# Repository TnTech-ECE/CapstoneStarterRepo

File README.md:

# Drone Tracking System
## Executive Summary

Drones have grown exceedingly popular in recent years due to both their novelty and capabilities. Unfortunately, not all drone users prioritize the safety and privacy of others while flying their drones, so to combat a rise in unsafe drone activities, the Federal Aviation Administration (FAA) created a regulation in 2023 requiring drones to emit a remote identification signal. Utilizing this regulation, this team is designing a drone tracking device that will notify the Tennessee Technological University (TTU) Police if an unauthorized drone enters the contiguous campus.

## Capabilities

The Drone tracker system is capable of storing RID information into a database. The database can send the required RID data to the camera where the camera uses it to point at a target. The camera then takes a picture and sends the image back to the database. The website will display the RID data from the database as well as a map of the target locations.

## Project Demonstration & Images
Project Demonstration Video

https://github.com/user-attachments/assets/e732b90d-667f-4436-8810-12add2868be1

https://github.com/user-attachments/assets/4852f584-2c88-4b63-8bfe-9ffbe9ff3a57

https://github.com/user-attachments/assets/bf1db036-6065-4abe-843b-16f495730f5c

#### Other video links:
[Camera Software System minimal functional prototype](https://www.youtube.com/shorts/UNsuytf4N7U)

[Website system](https://www.youtube.com/watch?v=dnVWmRdjKF0)

## About Us

### Team

From left to right:

[JieJun Stowell](https://www.linkedin.com/in/jiejun-s-4b34a8132/) is an computer engineering major student at Tennessee Technological University. He is intrestested in embedded system design development.

[Abe Perkins](https://www.linkedin.com/in/abraham-perkins-7436a6204/) is a student at Tennessee Technological University with major in computer engineering and a minor in math. His interests include hardware security, computer architecture, and machine learning. 

[Austin Williams](https://www.linkedin.com/in/austingwilliams/) is an electrical engineering major with a concentration in Power Systems. He is interested in power transmission and operations.

[Aaron Stewart](https://www.linkedin.com/in/aaronjs124) is an electrical engineering major with a concentration in Control Systems. He is interested in industrial production systems, mechatronics, and additive manufacturing methods.

[Sterling Sloan](https://www.linkedin.com/in/sterling-sloan-a848642a0/) is an electrical engineering major at Tennessee Technological University. He has interests in signal processing and optoelectronics.

[Meredith Nye](https://www.linkedin.com/in/meredith-nye-89455a1b5) is an electrical engineering major, mechatronics concentration and student-athlete at Tennessee Technological University with minors in math and biology. She is interested in prosthetics design, biomechanical engineering, and robotics.

### Faculty Supervisor

Dr. Jeffrey Austen is the faculty supervisor and stakeholder for the drone tracker project. He is a professor with the Electrical and Computer Engineering Department at Tennessee Technological University with specializations in signal processing and communication systems.

### Stakeholders

Dr. Jeffrey Austen

Tennessee Technological University Police

### Recognitions

We would like to recognize and thank Dr.Jeffrey Austen for his guidance and support as well as the [Spring 2024 Base Modular Robot Team](https://github.com/TnTech-ECE/Spring2024-Base-Modular-Robot) for their repository organization inspiration.

## Repo Organization

### [Reports](/Reports)
  - [Project Proposal](https://github.com/mrnye42/S24_Team1_DroneTracker/blob/main/Reports/Project%20Proposal%20Revisions.pdf) :the initial document for the project where the problem is defined and the goals for the project.
  - [Conceptual Design and Planning](https://github.com/mrnye42/S24_Team1_DroneTracker/blob/main/Reports/Conceptual%20Design%20and%20Planning%20Final.pdf) :gives a more detailed solution to the problem as well as subsystem breakdowns and a projected timeline and budget.
  - [Final Presentation](https://github.com/mrnye42/S24_Team1_DroneTracker/blob/main/Reports/Drone%20Tracker%20IAB%20Presentation%20Final.pdf) :a pdf version of the PowerPoint presentation given to the Advisory Board that showcases the entire project and contains video links to project demonstrations. 
  - [Poster](https://github.com/mrnye42/S24_Team1_DroneTracker/blob/main/Reports/Poster.pdf) :showcases the entire project. Was displayed at the senior design expo and will be framed in Brown Hall.
  - [Lessons Learned Presentations](/Reports/Lessons-Learned-Presentations) :folder contains a few of the team's individual lessons learned PowerPoint presentations and contain things that went wrong and advice for future students.

### [Documentation](/Documentation)
All documentation for the project is included in the above folder. Documentation includes all schematics, images, models, BOM, and designs used in the project.

The [Meeting Minutes](/Documentation/Meeting-Minutes) folder contains the dated minutes from weekly meetings and allows a quick view into the progress of the team.

[Signoffs](/Documentation/Signoffs) are used to finalize designs for each subsystem. This includes schematics, design decisions, BOM, and analysis.

The [Experimentation](/Documentation/Experimentation/) folder contains individual markdown files detailing experiments done by the team in order to prove the adherence to different system constraints.

The [Minimal Functionality Prototype document](https://github.com/mrnye42/S24_Team1_DroneTracker/blob/main/Documentation/Minimal%20Functionality%20Prototype%20Signoffs.pdf) contains the proposed minimal functionality requirements for the protype as well as Dr.Austen's feedback on them.

The [Final BOM](https://github.com/mrnye42/S24_Team1_DroneTracker/blob/main/Documentation/Final%20BOM.pdf) pdf contains all the ordered parts for the project.

The [Project Photos](/Documentation/Project-Photos) folder contains any photos (not technical images) from the project. Includes addtional pictures of the team.

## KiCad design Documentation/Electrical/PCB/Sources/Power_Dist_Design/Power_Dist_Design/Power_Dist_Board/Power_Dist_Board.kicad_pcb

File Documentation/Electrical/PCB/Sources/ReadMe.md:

- This contains the gerber files in order to purchase the input and error subsystem PCBs.
- ## Relevant design notes
- The polarity shown on the PCB design for the electrolytic capacitors is in a few cases backwards, therefore it is advised to read the traces and consult the schematic before any polarized 
  capacitors are soldered on the PCB.
- The I/O and supply ports were not placed on the PCB with ports therefore in order to connect the PCB to other elements it is recommended to consult the schematic and solder wires in the 
  appropriate places.

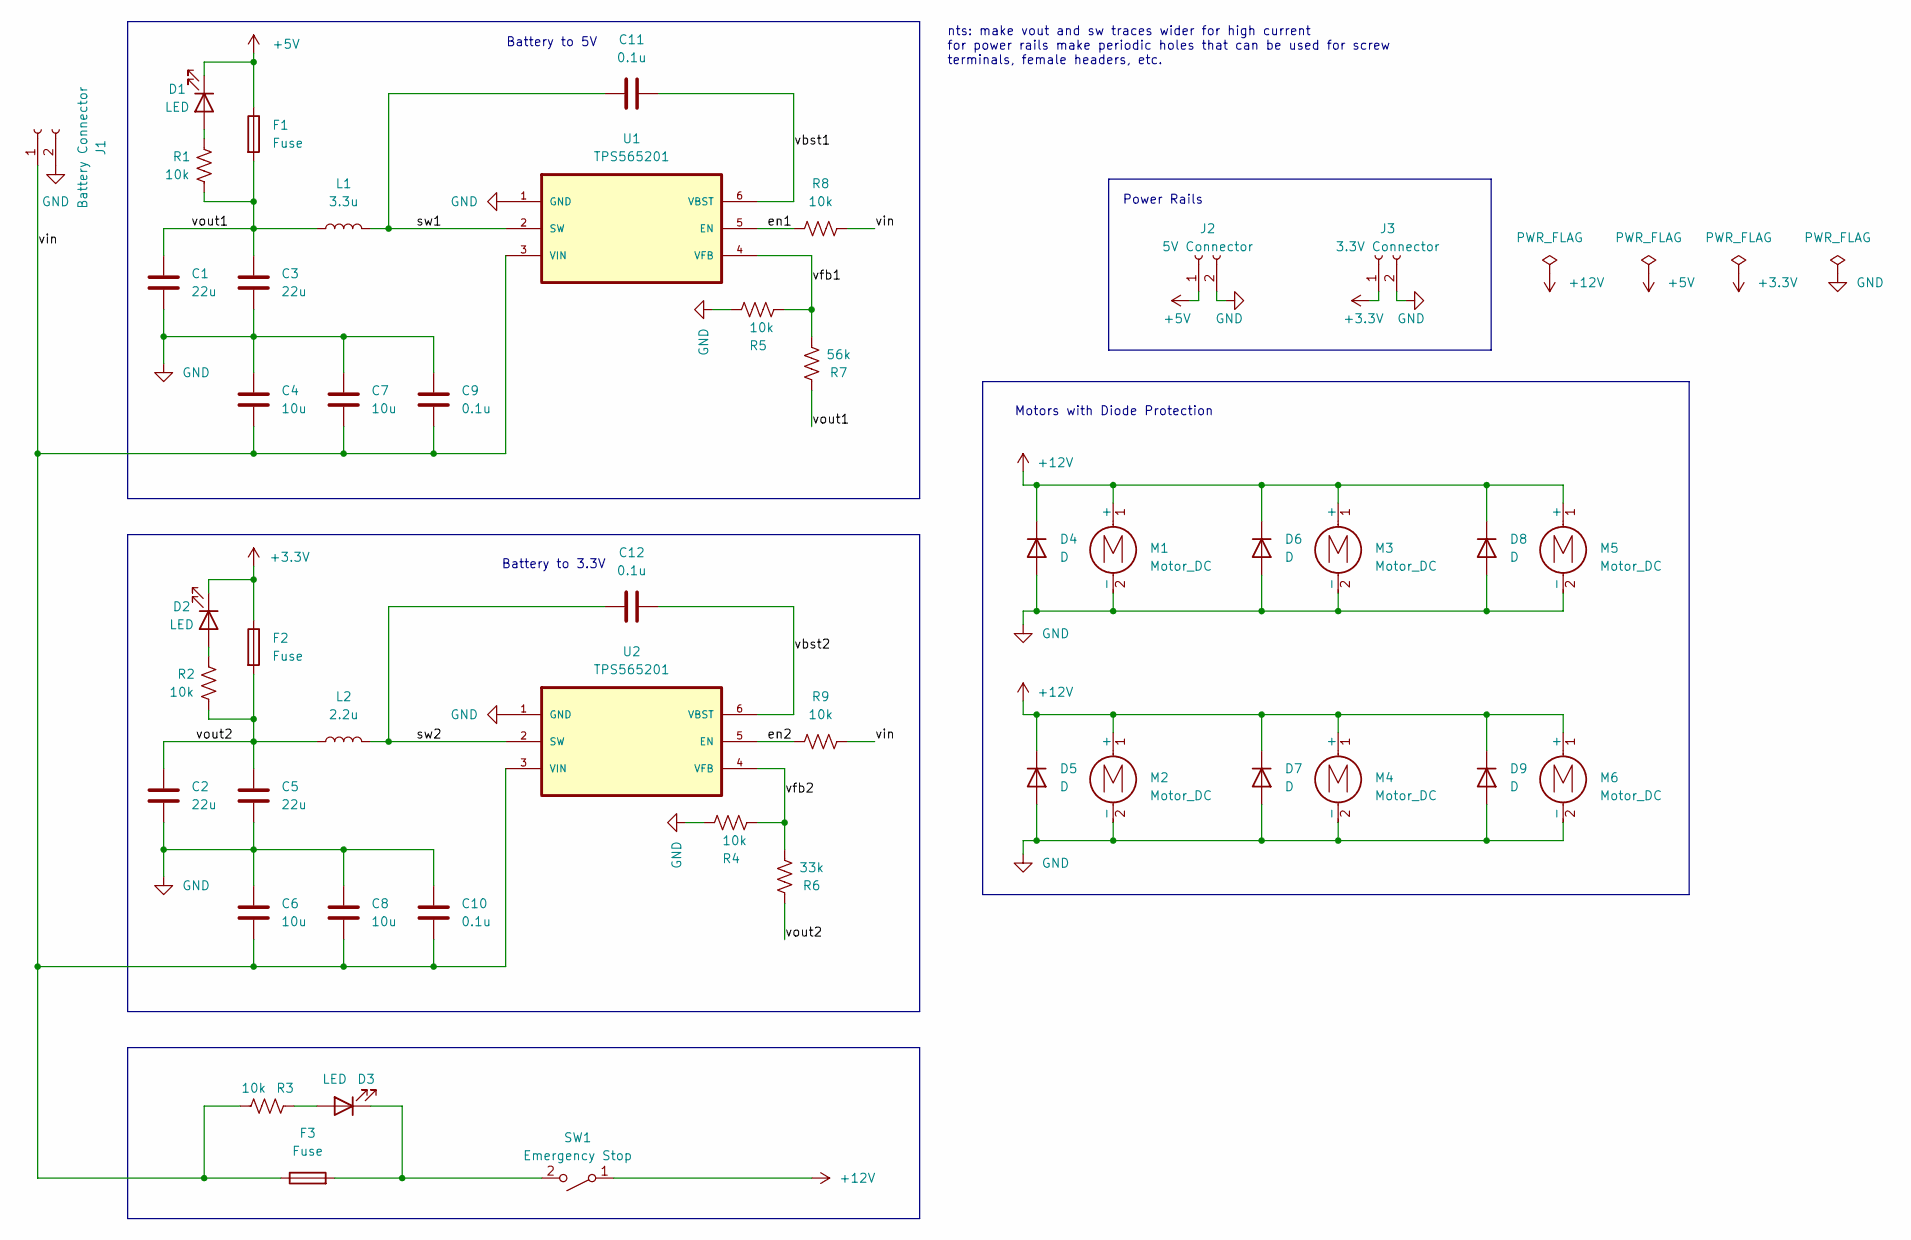
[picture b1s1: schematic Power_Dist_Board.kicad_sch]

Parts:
C1, C2, C3, C5: 22u; C_1206_3216Metric_Pad1.33x1.80mm_HandSolder
C4, C6, C7, C8: 10u; C_1206_3216Metric_Pad1.33x1.80mm_HandSolder
C9, C10, C11, C12: 0.1u; C_1206_3216Metric_Pad1.33x1.80mm_HandSolder
D1, D2, D3: LED; LED_1206_3216Metric_Pad1.42x1.75mm_HandSolder
D4, D5, D6, D7, D8, D9: D; DIO_RB051MM_ROM-M
F1, F2, F3: Fuse; Fuse_1206_3216Metric_Pad1.42x1.75mm_HandSolder
J1: Battery Connector; Molex_Screw_Term_0397730002
J2: 5V Connector; PhoenixContact_MSTBVA_2,5_2-G-5,08_1x02_P5.08mm_Vertical
J3: 3.3V Connector; PhoenixContact_MSTBVA_2,5_2-G-5,08_1x02_P5.08mm_Vertical
L1: 3.3u; R_1206_3216Metric_Pad1.30x1.75mm_HandSolder
L2: 2.2u; R_1206_3216Metric_Pad1.30x1.75mm_HandSolder
M1, M2, M3, M4, M5, M6: Motor_DC; Molex_Screw_Term_0397730002
R1, R2, R3, R4, R5, R8, R9: 10k; R_1206_3216Metric_Pad1.30x1.75mm_HandSolder
R6: 33k; R_1206_3216Metric_Pad1.30x1.75mm_HandSolder
R7: 56k; R_1206_3216Metric_Pad1.30x1.75mm_HandSolder
SW1: Emergency Stop; Molex_Screw_Term_0397730002
U1, U2: TPS565201

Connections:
+3.3V: D2.1 (K), F2.1, J3.1
+5V: D1.1 (K), F1.1, J2.1
+12V: D4.1 (K), D5.1 (K), D6.1 (K), D7.1 (K), D8.1 (K), D9.1 (K), M1.1 (+), M2.1 (+), M3.1 (+), M4.1 (+), M5.1 (+), M6.1 (+), SW1.1 (A)
/en1: R8.1, U1.5 (EN)
/en2: R9.1, U2.5 (EN)
/sw1: C11.1, L1.2, U1.2 (SW)
/sw2: C12.1, L2.2, U2.2 (SW)
/vbst1: C11.2, U1.6 (VBST)
/vbst2: C12.2, U2.6 (VBST)
/vfb1: R5.2, R7.1, U1.4 (VFB)
/vfb2: R4.2, R6.1, U2.4 (VFB)
/vin: C4.2, C6.2, C7.2, C8.2, C9.2, C10.2, F3.1, J1.1, R3.1, R8.2, R9.2, U1.3 (VIN), U2.3 (VIN)
/vout1: C1.1, C3.1, F1.2, L1.1, R1.1, R7.2
/vout2: C2.1, C5.1, F2.2, L2.1, R2.1, R6.2
GND: C1.2, C2.2, C3.2, C4.1, C5.2, C6.1, C7.1, C8.1, C9.1, C10.1, D4.2 (A), D5.2 (A), D6.2 (A), D7.2 (A), D8.2 (A), D9.2 (A), J1.2, J2.2, J3.2, M1.2 (-), M2.2 (-), M3.2 (-), M4.2 (-), M5.2 (-), M6.2 (-), R4.1, R5.1, U1.1 (GND), U2.1 (GND)
unnamed: D1.2 (A), R1.2
unnamed: D2.2 (A), R2.2
unnamed: D3.1 (K), F3.2, SW1.2 (B)
unnamed: D3.2 (A), R3.2

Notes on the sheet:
nts: make vout and sw traces wider for high current for power rails make periodic holes that can be used for screw terminals, female headers, etc.
Motors with Diode Protection
Battery to 5V
Battery to 3.3V
Power Rails

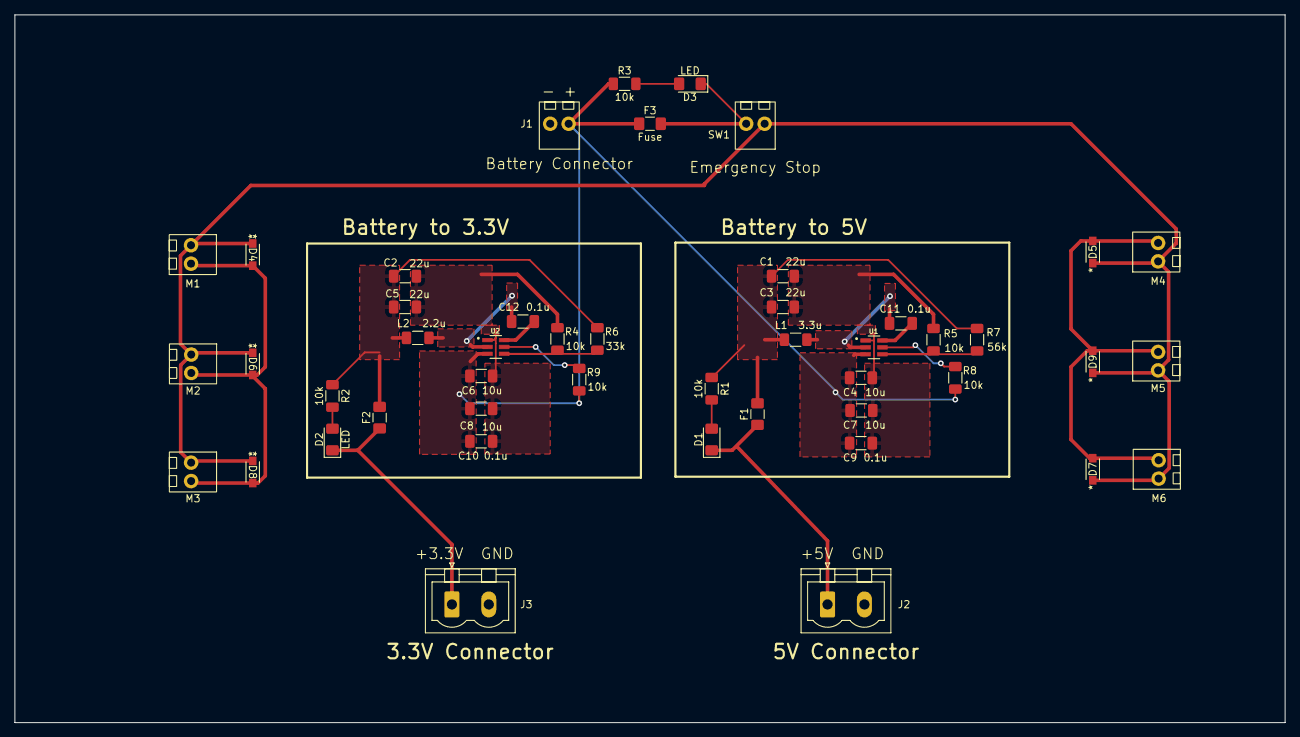
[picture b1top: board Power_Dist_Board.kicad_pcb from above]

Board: 2 copper layers, 175.0 x 97.5 mm, 47 parts (0 on the bottom side), 19 nets.

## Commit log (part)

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2024-11-13 Rename Minutes-2024-11-4.md to Minutes-2024-11-04.md
2024-11-13 Create Backups
    Backup folder for all software in project
2024-11-13 Add files via upload
    Backup 20241113
2024-11-14 Rename BOM_Group1.xlsx to Final Bill of Materials.xlsx
2024-11-14 Rename Capstone Lessons Learned PowerPoint.pptx to Meredith's Lessons Learned.pptx
2024-11-16 Rename CamScanner 11-15-2024 18.53.pdf to Minimal Functionality Prototype Signoffs.pdf
2024-11-16 Rename Minimal Functionality Prototype Signoffs.pdf to Minimal Functionality Prototype Signoffs.pdf
2024-11-17 Added constraint testing to experimental analysis for networking and head on system. Also fixed image links
2024-11-19 Update Experimental Analysis Updated.md
    Added critical constraint for velocity and acceleration subsystem
2024-11-19 Update Experimental Analysis Updated.md
    Added period at the end of constraint 3
2024-11-19 Update Experimental Analysis Updated.md
    added aiming system critical constraints
2024-11-19 Update CapstoneProject.ino
    Updated test code
2024-11-19 Update capstoneproject.h
    Updated for testing and more specific servo PWM changes
2024-11-19 Update CapstoneProject.ino
    Small updates to code
2024-11-19 Added networking and head on sensor constraints
2024-11-20 Create Camera Software - Testing Priority Statuses
2024-11-20 Update Experimental Analysis Updated.md
    Added Experimental Analysis for Velocity and Acceleration subsystem and constraints
2024-11-20 Update CapstoneProject.ino
    Networking code uncommented and brownout added, code was working before hand and was used for experimental analysis
2024-11-20 Update capstoneproject.h
    Appropriate updates to accompany main file
2024-11-20 Rename Camera_Hardware.md to Camera_Hardware - Testing Priority Constraints.md
2024-11-20 Create Website - Experimental Analysis
2024-11-20 Rename Website - Experimental Analysis to Website - Experimental Analysis.md
2024-11-20 Create Power Systems - Experimental Analysis
2024-11-20 Update Power Systems - Experimental Analysis
2024-11-20 Rename Power Systems - Experimental Analysis to Power Systems - Experimental Analysis.md
2024-11-20 Added last week minutes
2024-11-20 Create Database - Experimental Analysis
    Experimental Analysis started
2024-11-20 Delete Documentation/Experimentation/Database - Experimental Analysis
    Removing Database - Experimental Analysis file
2024-11-20 Create Database - Experimental Analysis
    Database - Experimental Analysis documentation started
2024-11-21 Update Database - Experimental Analysis.md
    update
2024-11-21 Create Receiver - Experimental Analysis
2024-11-21 Update Database - Experimental Analysis.md
    Experimental Result update
2024-11-21 Update Database - Experimental Analysis.md
    Experimental Analysis result unit update
2024-11-21 Update Database - Experimental Analysis.md
    Experimental Analysis update
2024-11-21 Update Database - Experimental Analysis.md
    Constraint 1 update
2024-11-21 Update Database - Experimental Analysis.md
    Experimental Procedure - Constraint 1 update
2024-11-21 Update Database - Experimental Analysis.md
    Constraint 1 result update
2024-11-21 Update Database - Experimental Analysis.md
    update fix
2024-11-21 Update Database - Experimental Analysis.md
    Constrain 1 example data update
2024-11-21 Update Database - Experimental Analysis.md
    Experimental data update
2024-11-21 Update Database - Experimental Analysis.md
    Conclusions update
2024-11-21 Update Database - Experimental Analysis.md
    Gramma update
2024-11-22 Rename 20241121_19h27m59s_grim.png to terminal.png
2024-11-25 Rename Poster Specifications.md to Final Poster Specifications.md
2024-11-25 Rename Project Proposal Template.md to Project Proposal Specifications.md
2024-11-25 Rename Individual Presentation.md to Individual Presentation Specifications.md
2024-11-25 Rename Final Report Template.md to Final Report Specifications.md
2024-11-25 Rename Final Presentation Template.md to Final Presentation Specifications.md
2024-11-25 Rename Experimentation Template.md to Experimentation Specifications.md
2024-11-25 Rename Detailed Design Template.md to Detailed Design Specifications.md
2024-11-25 Rename Conceptual Design Template.md to Conceptual Design Specifications.md
2024-11-26 solidified esp code
2024-11-27 Update CapstoneProject.ino
    Networking input now reading and able to use line num
2024-11-27 Update capstoneproject.h
    ServoPin1 changed
2024-11-27 Update capstoneproject.h
    All code working refixed issues address in previous versions that resurfaced
2024-11-27 Update CapstoneProject.ino
    Working code for networking ,servo, and range
2024-12-03 Rename Team1_Final_Poster_Drone_Tracker_Project.pdf to Final Poster.pdf
2024-12-03 Rename Team1_Final_Poster_Drone_Tracker_Project.pdf to Poster.pdf
2024-12-06 Update README.md
    explain function of code.
2024-12-07 Update README.md
    description of MariaDB tables update
2025-01-16 Update and rename Experimentation Specifications.md to Experimental Analysis Specifications
2025-01-16 Rename Experimental Analysis Specifications to Experimental Analysis Specifications.md
2025-09-02 Update Team Contract Specification.md
    Updated Unique Roles Wording
2025-09-04 draft of contract
2025-09-04 wip of main readme
2025-09-04 fixed spelling errors in my bio
2025-09-04 made signatures on own lines
2025-09-04 Update README.md added supervisor
2025-09-04 added stake holder dseciption
2025-09-04 new line for stake holders
2025-09-04 linked lockinvar about us page
2025-09-04 Update README.md
    Salient Outcome description added
2025-09-05 Update Team Contract Specification.md
    qUEEN
2025-09-05 Update Team Contract Specification.md
    I am on the team - qUEEN
2025-09-08 proofread/revised and added my signature
2025-09-08 Update Team Contract Specification.md
    Signature
2025-09-08 Update Project Proposal Specifications.md
    Spelling Correction
2025-09-08 Update Team Contract Specification.md
    the right way
2025-09-08 Update Team Contract Specification.md
    LFB sign off. Looks Good Guys.
2025-09-09 Update README.md
    Testing Webhook
2025-09-15 First draft of meeting minutes
2025-09-15 Add stuff from meeting with Storm
2025-09-16 First two solutions for Existing Solutions
2025-09-16 Finished half(ish) of Survey of Existing Solutions
    Needs further research on DIY solutions and an explanation for the DIY section at the top
2025-09-16 syntax fixes
2025-09-16 reverted syntax "fixes"
2025-09-16 Update Project Proposal Specifications.md
    kind of a rough draft potentially
2025-09-16 Update Project Proposal Specifications.md
    added comment on what I believe needs to be added and also rephrased a sentence to sound better
2025-09-16 Update Project Proposal Specifications.md
    I did my part :)
2025-09-17 Copied Lewis's work for Existing Solutions
2025-09-17 Update Project Proposal Specifications.md
    over the board
2025-09-17 Fixed issue with existing solutions number 6
2025-09-19 First part of Measures of Success
    Still need to do short intro and conclusion of section, as well as add two or so more sections
2025-09-19 Swapped DIY and Industrial Solutions
    Thank you Lewis i forgot
2025-09-19 Formatting Fixes
2025-09-19 Finished Measures of Success section
2025-09-21 Update Project Proposal Specifications.md
    Added the specific and broader implications
2025-09-21 Update Project Proposal Specifications.md
    personnel finished, looking at the formatting on my branch before adding it
2025-09-21 Update Project Proposal Specifications.md
    tweaked it
2025-09-21 Update Project Proposal Specifications.md
    redid personnel
2025-09-22 Added Specifications and Constraints
2025-09-22 Update Project Proposal Specifications.md
    Updated Resources + Budget
2025-09-22 Update Project Proposal Specifications.md
    changed some things in budget
2025-09-22 Update Project Proposal Specifications.md
    sources
2025-09-22 Update Project Proposal Specifications.md
    checking if Gantt chart formatting worked
2025-09-22 Update Project Proposal Specifications.md
    trying Gantt chart again
2025-09-22 Update Project Proposal Specifications.md
    trying to get the colors back
2025-09-22 Update Project Proposal Specifications.md
    fixed problem with image
2025-09-22 Update Project Proposal Specifications.md
    updating gantt chart based on date changes
2025-09-22 Update Project Proposal Specifications.md
    I accidentally deleted specifications and constraints, so I think this should hopefully fix it
2025-09-22 Update Project Proposal Specifications.md
    5
2025-09-24 Updated Introduction
2025-09-24 help me
2025-09-24 Added individual contributions and team name
2025-09-24 noah haha
2025-09-24 Update Project Proposal Specifications.md
    Contributions
2025-09-25 Added some spaces for testing
